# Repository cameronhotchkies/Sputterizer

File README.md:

# Sputterizer
Signal Generator for Eurorack Synthesizers
https://www.greenfacelabs.com/

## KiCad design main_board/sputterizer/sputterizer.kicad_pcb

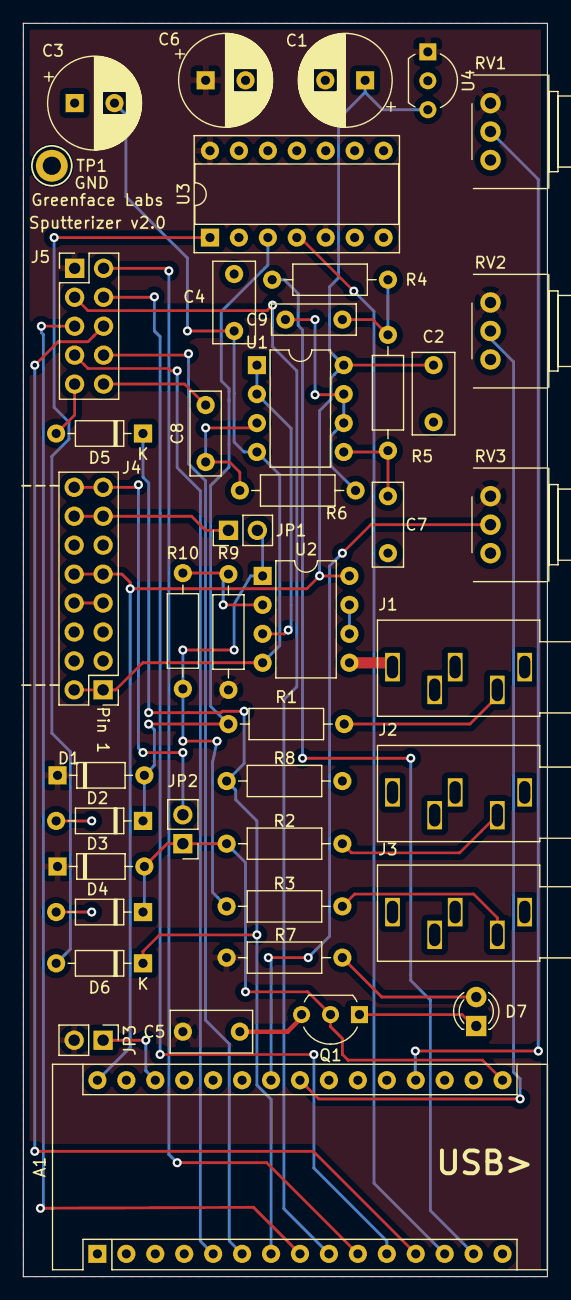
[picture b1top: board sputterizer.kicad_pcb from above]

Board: 2 copper layers, 46.0 x 110.0 mm, 44 parts (0 on the bottom side), 37 nets.

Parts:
A1: Arduino_Nano_v3.x; Arduino_Nano
C1, C3, C6: 100uF; CP_Radial_D8.0mm_P3.50mm
C2, C4, C5: 100nF; C_Rect_L7.0mm_W3.5mm_P5.00mm
C7: 10nF; C_Rect_L7.2mm_W2.5mm_P5.00mm_FKS2_FKP2_MKS2_MKP2
C8, C9: 100nF; C_Rect_L7.2mm_W2.5mm_P5.00mm_FKS2_FKP2_MKS2_MKP2
D1, D2, D3, D4: SB120; D_DO-35_SOD27_P7.62mm_Horizontal
D5, D6: 1N4148; D_DO-35_SOD27_P7.62mm_Horizontal
D7: LED; LED_D3.0mm
J1, J2, J3: SJ1-3535; Jack_3.5mm_CUI_SJ1-3535NG_Horizontal_RectangularHoles
J4: 2X8 Header; PinHeader_2x08_P2.54mm_Vertical
J5: Conn_02x05_Odd_Even; PinHeader_2x05_P2.54mm_Vertical
JP1, JP2, JP3: Conn_01x02_Male; PinHeader_1x02_P2.54mm_Vertical
Q1: BS170; TO-92L_Inline_Wide
R1: 10K; R_Axial_DIN0207_L6.3mm_D2.5mm_P10.16mm_Horizontal
R2, R3: 470; R_Axial_DIN0207_L6.3mm_D2.5mm_P10.16mm_Horizontal
R4: 17.8K; R_Axial_DIN0207_L6.3mm_D2.5mm_P10.16mm_Horizontal
R5: 140K; R_Axial_DIN0207_L6.3mm_D2.5mm_P10.16mm_Horizontal
R6: 15.8K; R_Axial_DIN0207_L6.3mm_D2.5mm_P10.16mm_Horizontal
R7: 1K; R_Axial_DIN0207_L6.3mm_D2.5mm_P10.16mm_Horizontal
R8: 20K; R_Axial_DIN0207_L6.3mm_D2.5mm_P10.16mm_Horizontal
R9, R10: 10.0K; R_Axial_DIN0207_L6.3mm_D2.5mm_P10.16mm_Horizontal
RV1, RV2, RV3: 10K; Potentiometer_Bourns_PTD901_Single_Horizontal
TP1: TestPoint; TestPoint_Keystone_5005-5009_Compact
U1, U2: NE5532; DIP-8_W7.62mm
U3: CD4013BE; DIP-14_W7.62mm_Socket
U4: L78L05_TO92; TO-92L_Inline_Wide

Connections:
+5V: C5.1, C6.1, D1.1, D3.1, J5.1, JP3.2, R7.2, R9.1, RV1.3, RV2.3, RV3.3, U3.5, U3.14, U4.1
+12V: A1.30, C1.1, C2.1, J4.9, J4.10, U1.8, U2.8, U4.3
-12V: C3.2, C4.2, J4.1, J4.2, U1.4, U2.4
/CV: J4.13, J4.14, JP1.1
/Gate: J4.15, J4.16, JP2.2
GND: A1.4, A1.29, C1.2, C2.2, C3.1, C4.1, C5.2, C6.2, C7.2, C8.2, D2.2, D4.2, J1.1, J1.3, J1.4, J1.5, J2.1, J2.3, J2.5, J3.1, J3.3, J3.5, J4.3, J4.4, J4.5, J4.6, J4.7, J4.8, J5.10, Q1.3, R8.1, RV1.1, RV2.1, RV3.1, TP1.1, U2.5, U3.6, U3.7, U3.8, U3.9, U3.10, U3.11, U4.2
unnamed: A1.5, J5.7
unnamed: A1.6, J5.8
unnamed: A1.7, D5.1, D6.1, R8.2
unnamed: A1.8, J5.5
unnamed: A1.9, J5.3
unnamed: A1.10, J5.2
unnamed: A1.11, J5.4
unnamed: A1.12, J5.6
unnamed: A1.13, U3.4
unnamed: A1.14, R4.2
unnamed: A1.16, D3.2, D4.1, JP2.1, Q1.2, R2.2
unnamed: A1.19, RV1.2
unnamed: A1.23, RV2.2
unnamed: A1.24, RV3.2
unnamed: A1.28, JP3.1
unnamed: C7.1, R5.1, U1.5
unnamed: C8.1, R6.1, U1.3
unnamed: C9.1, R6.2, U1.6, U1.7
unnamed: C9.2, R4.1, R5.2
unnamed: D1.2, D2.1, R1.1, U3.3
unnamed: D5.2, J5.9
unnamed: D6.2, U3.1
unnamed: D7.1, Q1.1
unnamed: D7.2, R7.1
unnamed: J1.2, R1.2
unnamed: J2.2, R2.1
unnamed: J3.2, R3.1
unnamed: JP1.2, R3.2, R10.2, U2.1
unnamed: R9.2, R10.1, U2.2
unnamed: U1.1, U1.2, U2.3
unnamed: U2.6, U2.7

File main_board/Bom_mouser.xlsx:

Manufacturer Part Number | Manufacturer | Customer Reference | Reference Designator | Quantity | Digi-Key Part Number
A000005 | Arduino | Arduino_Nano_v3.x | A1 | 1 | 1050-1001-ND
SR215C104KAA | AVX Corporation | 100nF | C2 C4 C5 | 3
EKRG350ELL101MH09D | United Chemi-Con (UCC) | 100uF | C6 C1 C3 | 3 | 1189-3982-ND
R82EC2100DQ50J | KEMET | 10nF | C7 | 1
R82DC3100DQ50J | KEMET | 100nF | C9 C8 | 2
SB120-T | Diodes Incorporated | SB120 | D1 D2 D3 D4 | 4
1N4448 | ON Semiconductor | 1N4448 | D5 D6 | 2
151031VS06000 | Wurth Electronics Inc. | GREEN LED | D7 | 1
SJ1-3535 | CUI Devices | SJ1-3535 | J1 J2 J3 | 3
649-77313-418-16LF | Amphenol ICC (FCI) | 2X8 Header | J4 | 1
67997-210HLF | Amphenol ICC (FCI) | Conn_02x05_Odd_Even | J5 | 1
M20-9990245 | Harwin Inc. | Conn_01x02_Male | JP1 JP2 JP3 | 3
BS170-D75Z | ON Semiconductor | BS170 | Q1 | 1
CFR-25JR-52-10K | Yaego | 10K | R1 | 1
MRS25000C1002FCT00 | Vishay BC Components | 10.0K | R10 R9 | 2
CFR-25JT-52-470R | Yaego | 470 | R2 R3 | 2
MFR-25FBF52-17K8 | Yaego | 17.8K | R4 | 1
MRS25000C1403FCT00 | Vishay BC Components | 140K | R5 | 1
MFR-25FBF52-15K8 | Yaego | 15.8K | R6 | 1
CFR-25JB-1K0 | Yaego | 1K | R7 | 1
CFR-25JT-52-20K | Yaego | 20K | R8 | 1
PTD901-1015K-B103 | Bourns Inc. | 10K | RV1 RV2 RV3 | 3
5006 | Keystone Electronics | TestPoint | TP1 | 1 | 36-5006-ND
SA5532AP | Texas Instruments | NE5532 | U1 U2 | 2
CD4013BE | Texas Instruments | CD4013BE | U3 | 1
MC78L05BP-AP | Micro Commercial Co | L78L05_TO92 | U4 | 1
110-47-308-41-001000 | Mill-Max | CONN IC DIP SOCKET 8POS TIN | K1 K2 | 2
110-47-314-41-001000 | Mill-Max | CONN IC DIP SOCKET 14POS TIN | K3 | 1
K103M15X7RF53L2 | Vishay BC Components | .01uF | SC1 SC2 | 2
ECE-A1EKA470I | Panasonic Electronic Components | 47uF | SC4 | 1
SR215C104KAA | AVX Corporation | .1uF | SC5 SC3 | 2
151031SS04000 | Wurth Electronics Inc. | Red LED | SD1 SD2 SD3 SD4 SD5 SD6 SD7 SD8 SD9 SD10 SD11 SD12 | 12
67997-210HLF | Amphenol ICC (FCI) | Conn_02x05_Odd_Even | SJ1 | 1
CFR-25JB-1K0 | Yaego | 1K | SR7 | 1
CFR-25JR-52-10K | Yaego | 10K | SR3 SR5 SR1 SR2 | 4
CFR-25JT-52-2K2 | Yaego | 2.2K | SR4 SR6 | 2
PEC11R-4315F-S0012 | Bourns Inc. | PEC11R | SSW1 | 1
TLC5916IN | Texas Instruments | TLC5916 | SU1 SU2 | 2
110-47-316-41-001000 | Mill-Max | CONN IC DIP SOCKET 16POS TIN | SK1 SK2 | 2
IDSD-05-D-03.00-T | Samtec | Cable | SCB1 | 1
HCSD-08-D-12.00-01-N-G | Samtec | 16 Pos Cable | SCB2
971070155 | Wurth Electronics Inc. |  | SA1 SA2 SA3 SA4 | 4
4687 | Keystone Electronics |  | SB1 SB2 SB3 SB4 | 4
29331 | Keystone Electronics |  | SC1 SC2 SC3 SC4 | 4
705820060 | Wurth Electronics Inc. | LED Standoff 6mm | SL1 SL2 SL3 SL4 SL5 SL6 SL7 SL8 SL9 SL10 SL11 SL12 | 12
1221-L | Davies Moulding | Knob | KN1 KN2 KN3 KN4 | 4
450-CK1560 | Eagle Plastic Devices | Knob | KN5 | 1

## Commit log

2019-06-02 Create Sputterizer Repository
2019-06-02 Checking in some files
2019-06-02 Adds files
2019-06-03 Adds Front Panel
2019-06-04 Latest changes.
2019-06-04 Gerber File
2019-06-10 First commit from VS
2019-06-11 Changes to code and adds drill to gerber
2019-06-11 Changes to gitignore
2019-06-17 Changes to board and code
2019-06-25 New design and code.
2019-07-06 New code and BOM
2019-08-11 Improvements to triggering. Adds updater.
2019-08-11 New update.bat
2019-09-01 Safety Checkin
2020-03-03 Latest checkin
2020-08-12 version 3.0
2020-08-18 Adds updater.zip to gitignore
